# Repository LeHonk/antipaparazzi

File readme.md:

# Antipaparazzi device

This project is intended to be an anti-paparazzi device.
The idea is to detect if a camera system or other optical system is directed towards the device.
The detection is done by scanning the surroundings with a laser beam, and detect any reflections.
All optical systems will have a retro-reflex, directing the reflected beam in the opposing direction of the incoming beam, 
e.g. back to the device.

## Phased-Locked-Loop design

Natural speed of the combination of motor and drive wheel results in a scanning speed of 16 Hz.
Multiplied by 360 (for 1 degree of angular resolution) means that the clock should be around 5.8 kHz.

Choosing oscillator components according to HFE4046B datasheet section 11.1 (VCO without frequency offset)with a 5760 Hz f0 gives;
	R1 = 100 kOhm	or	R1 = 10 kOhm
	C1 = 800 pF		C1 = 7000 pF

With assumed limits of 12 to 20 Hz the clock limits become 4320 resp. 7200 Hz. (fmax/fmin = 1.667)
Choosing components (VFO with frequency offset) leads to values:
	R1 = 80 kOhm
	R2 = 100 kOhm
	C1 = 2000 pF

Components at hand:
	R1 = 10 kOhm
	C1 = 10 nF

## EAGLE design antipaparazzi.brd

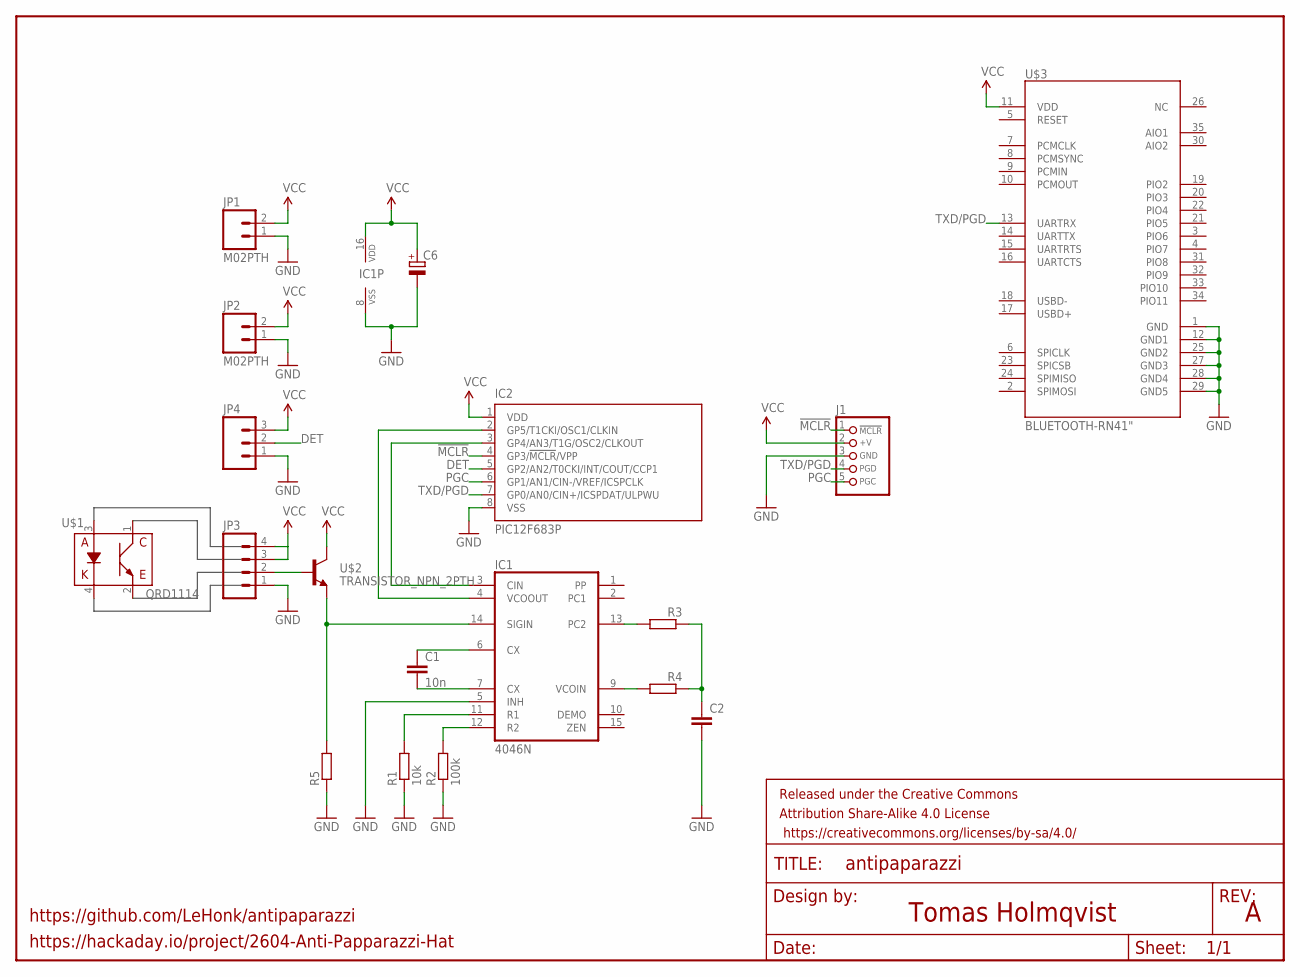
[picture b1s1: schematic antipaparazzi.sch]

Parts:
C1: 10n; C025_050-025X075
C2: C-EU025_050-025X075; C025_050-025X075
C6: CPOL-EUE2.5-6; E2,5-6
FRAME1: FRAME-LETTER; CREATIVE_COMMONS
IC1: 4046N; DIL16
IC2: PIC12F683P; DIL8
J1: CON_HEADER_PRG_PIC_ICSP0.1INCH_B; HEADER_PRG_1X05_ICSP_B
JP1, JP2: M02PTH; 1X02
JP3: M04PTH; 1X04
JP4: M03PTH; 1X03
R1: 10k; 0207/2V
R2: 100k; 0207/2V
R3, R4, R5: R-EU_0207/2V; 0207/2V
U$1: QRD1114
U$2: TRANSISTOR_NPN_2PTH; TO-92
U$3: BLUETOOTH-RN41"; RN41

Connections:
!MCLR: IC2.4 (GP3/!MCLR!/VPP), J1.1 (/MCLR)
DET: IC2.5 (GP2/AN2/T0CKI/INT/COUT/CCP1), JP4.2
GND: C2.2, C6.-, IC1.5 (INH), IC1.8 (VSS), IC2.8 (VSS), J1.3 (GND), JP1.1, JP2.1, JP3.1, JP4.1, R1.1, R2.1, R5.1, U$3.1 (GND), U$3.12 (GND1), U$3.25 (GND2), U$3.27 (GND3), U$3.28 (GND4), U$3.29 (GND5)
unnamed: IC1.4 (VCOOUT), IC2.2 (GP5/T1CKI/OSC1/CLKIN)
unnamed: IC1.3 (CIN), IC2.3 (GP4/AN3/T1G/OSC2/CLKOUT)
unnamed: C1.1, IC1.6 (CX)
unnamed: C1.2, IC1.7 (CX)
unnamed: IC1.12 (R2), R2.2
unnamed: IC1.11 (R1), R1.2
unnamed: IC1.14 (SIGIN), R5.2, U$2.3 (E)
unnamed: C2.1, R3.1, R4.1
unnamed: IC1.13 (PC2), R3.2
unnamed: IC1.9 (VCOIN), R4.2
unnamed: JP3.2, U$2.2 (B)
PGC: IC2.6 (GP1/AN1/CIN-/VREF/ICSPCLK), J1.5 (PGC)
TXD/PGD: IC2.7 (GP0/AN0/CIN+/ICSPDAT/ULPWU), J1.4 (PGD), U$3.13 (UARTRX)
VCC: C6.+, IC1.16 (VDD), IC2.1 (VDD), J1.2 (+V), JP1.2, JP2.2, JP3.3, JP3.4, JP4.3, U$2.1 (C), U$3.11 (VDD)

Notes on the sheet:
Tomas Holmqvist
https://hackaday.io/project/2604-Anti-Papparazzi-Hat
https://github.com/LeHonk/antipaparazzi

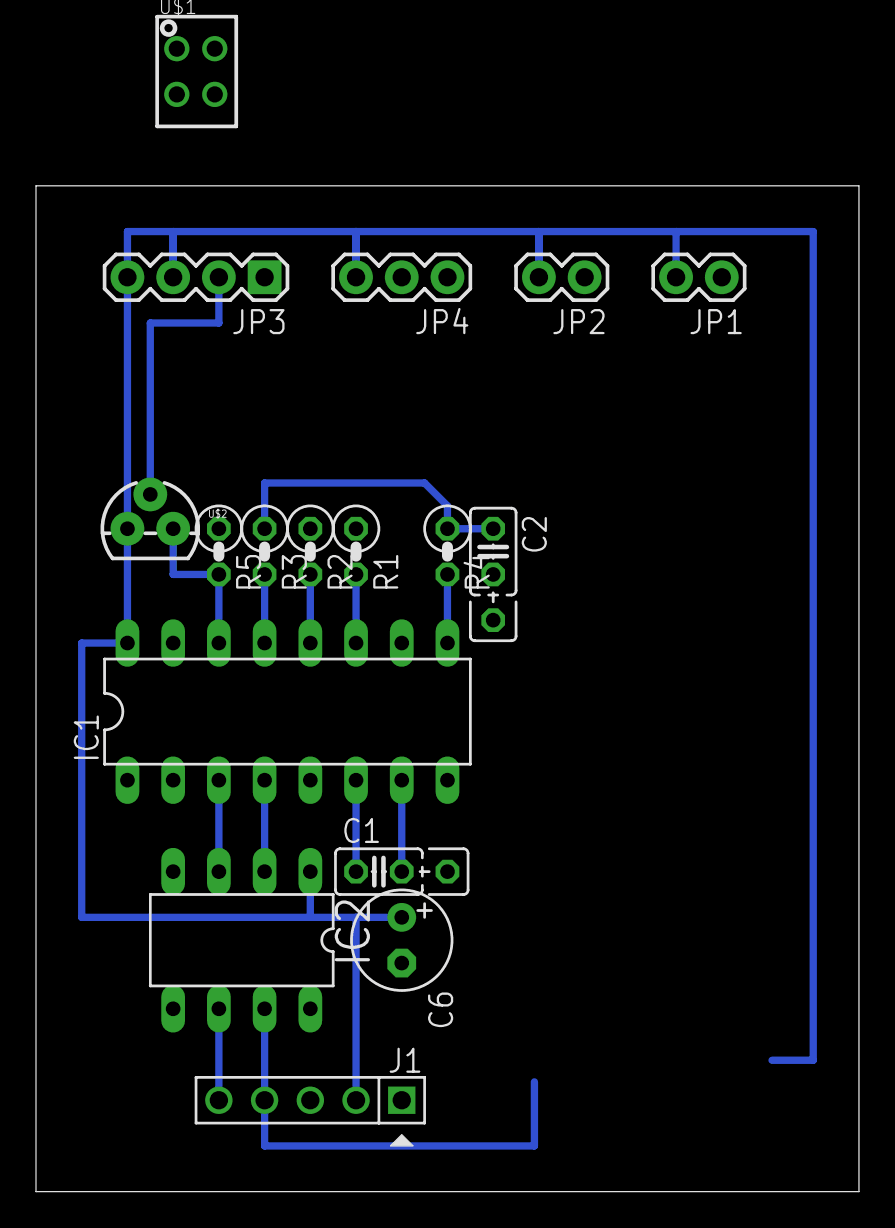
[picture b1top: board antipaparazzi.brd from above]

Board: 2 copper layers, 45.7 x 55.9 mm, 19 parts (1 on the bottom side), 17 nets.

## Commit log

2008-01-01 Added scan head design
2014-01-02 First attempt
2014-01-02 1:st Working revision
    Added MCRL release on install
    Enabled interrupts
2014-01-04 Added detection
    Detection via polled interruptflag.
    Detection reported via software bit-banged uart @ 9600 baud
2014-01-13 Added .stl to ignore-file
2014-01-14 Minor tweaks
2014-01-14 Added gcode file to ignore file
2014-01-15 Added extra cable channel
    Moved set screw hole out of belt drive groove.
    Edited some comments
2014-01-18 Minor edits
2014-01-21 Reimplemented in asm for faster interrupt response
2014-05-18 Functioning bitbang uart
2014-05-27 No interrupt execution, why?
2014-05-27 Switched to gputils toolchain
2014-07-07 Bussywait "interupt" implementation
2014-07-23 Working interrupts, yheay.
    Damn you bankselect.
2014-07-27 Working
    But; small detection pulses on GP2 are missed by IOC system (polled at Q3)
2014-08-21 Added system design document
2014-08-25 Added schematic and board
    In an initial rendering of whats on the breadboard
    Component values TBD.
2015-06-17 Added stl generation and file

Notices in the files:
parts and their libraries:
SparkFun-Sensors: Licensing: CC v3.0 Share-Alike You are welcome to use this library for commercial purposes.
SparkFun-Aesthetics: Released under the Creative Commons Attribution Share-Alike 4.0 License
SparkFun-Aesthetics: https://creativecommons.org/licenses/by-sa/4.0
